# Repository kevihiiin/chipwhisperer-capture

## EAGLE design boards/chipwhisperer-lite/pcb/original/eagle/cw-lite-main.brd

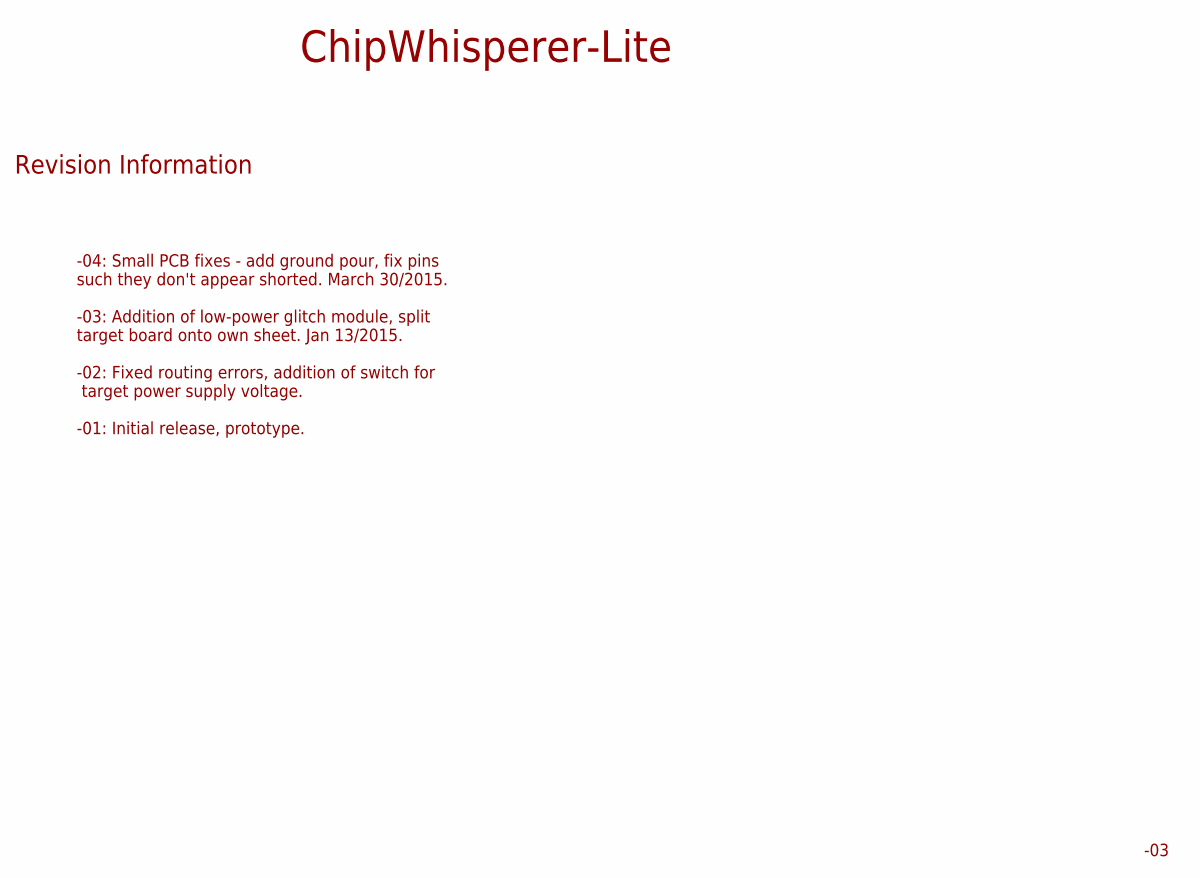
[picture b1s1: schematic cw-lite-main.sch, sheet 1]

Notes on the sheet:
-04: Small PCB fixes - add ground pour, fix pins such they don't appear shorted. March 30/2015. -03: Addition of low-power glitch module, split target board onto own sheet. Jan 13/2015. -02: Fixed routing errors, addition of switch for target power supply voltage. -01: Initial release, prototype.
ChipWhisperer-Lite
Revision Information

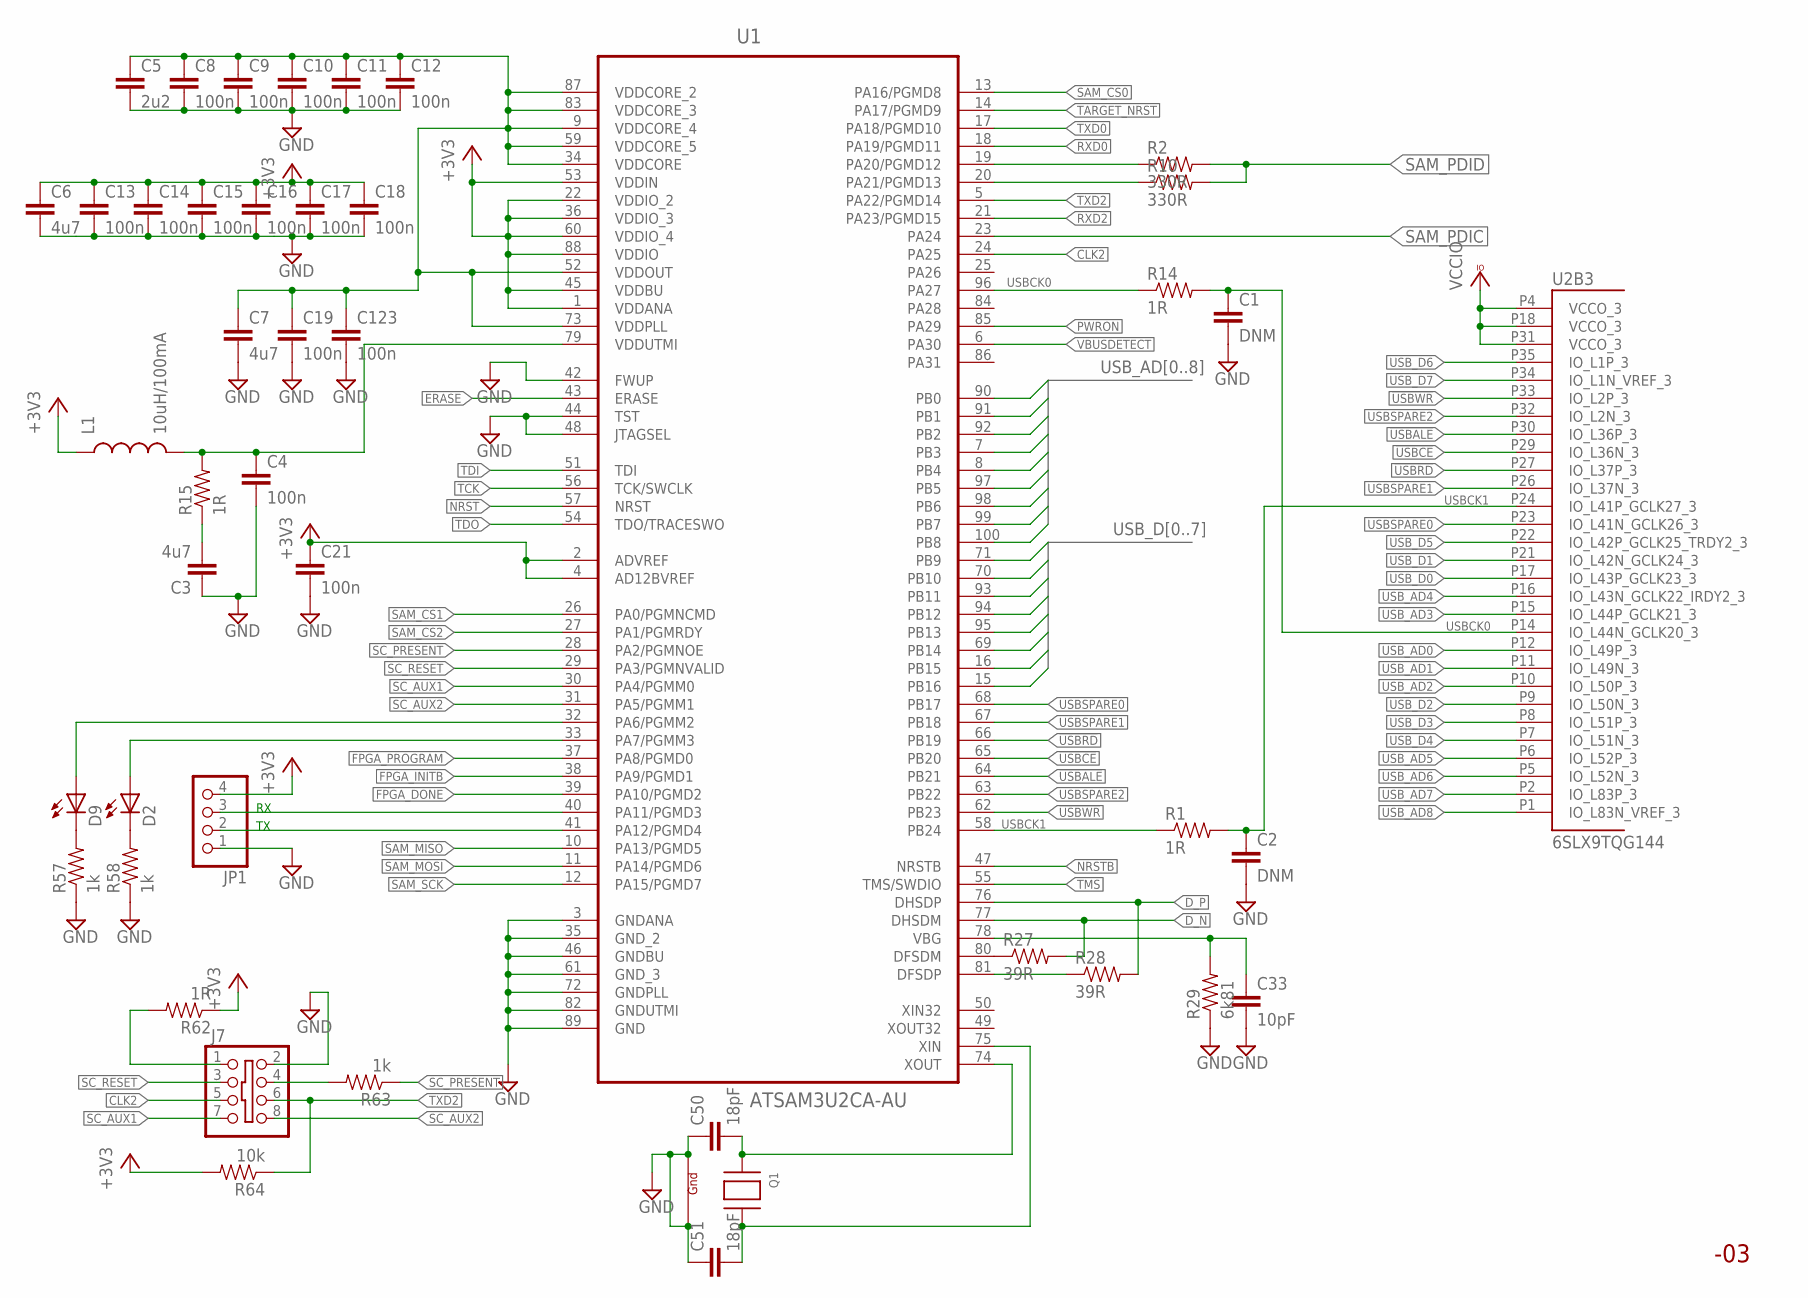
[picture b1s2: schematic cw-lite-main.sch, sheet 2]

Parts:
C1, C2: DNM; 0402C
C3, C6, C7: 4u7; 0603C
C4, C8, C9, C10, C11, C12, C13, C14, C15, C16, C17, C18, C19, C21, C123: 100n; 0402C
C5: 2u2; 0603C
C33: 10pF; 0603C
C50, C51: 18pF; 0402C
D2, D9: LED0603; LED-0603
J7: SHROUD_2X4EDGE; PINSHRD_EDGE_2X04.PAC
JP1: PINHD-1X4; 1X04
L1: 10uH/100mA; 0603
Q1: XTAL-4ABM8G; NX3225; MPN ABM8G-12.000MHZ-4Y-T3
R1, R14: 1R; 0402R
R2, R10: 330R; 0402R
R15, R62: 1R; 0603R
R27, R28: 39R; 0603R
R29: 6k81; 0402R
R57, R58, R63: 1k; 0603R
R64: 10k; 0603R
U1: ATSAM3U2CA-AU; QFP50P1600X1600X160-100N
U2: 6SLX9TQG144; TQ144; MPN XC6SLX9-3TQG144C

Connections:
!USBALE: U1.64 (PB21), U2.P30 (IO_L36P_3)
!USBCE: U1.65 (PB20), U2.P29 (IO_L36N_3)
!USBRD: U1.66 (PB19), U2.P27 (IO_L37P_3)
!USBWR: U1.62 (PB23), U2.P33 (IO_L2P_3)
+3V3: C6.1, C13.1, C14.1, C15.1, C16.1, C17.1, C18.1, C21.1, JP1.4, L1.1, R62.1, R64.2, U1.1 (VDDANA), U1.2 (ADVREF), U1.4 (AD12BVREF), U1.22 (VDDIO_2), U1.36 (VDDIO_3), U1.45 (VDDBU), U1.53 (VDDIN), U1.60 (VDDIO_4), U1.88 (VDDIO); also elsewhere on the board
CLK2: J7.5, U1.24 (PA25); also elsewhere on the board
D_N: R27.2, U1.77 (DHSDM); also elsewhere on the board
D_P: R28.2, U1.76 (DHSDP); also elsewhere on the board
ERASE: U1.43 (ERASE); also elsewhere on the board
FPGA_DONE: U1.39 (PA10/PGMD2); also elsewhere on the board
FPGA_INITB: U1.38 (PA9/PGMD1); also elsewhere on the board
FPGA_PROGRAM: U1.37 (PA8/PGMD0); also elsewhere on the board
GND: C1.2, C2.2, C3.1, C4.2, C5.2, C6.2, C7.2, C8.2, C9.2, C10.2, C11.2, C12.2, C13.2, C14.2, C15.2, C16.2, C17.2, C18.2, C19.2, C21.2, C33.2, C50.1, C51.1, C123.2, J7.2, JP1.1, Q1.2 (G1), Q1.4 (G2), R29.1, R57.1, R58.1, U1.3 (GNDANA), U1.35 (GND_2), U1.42 (FWUP), U1.44 (TST), U1.46 (GNDBU), U1.48 (JTAGSEL), U1.61 (GND_3), U1.72 (GNDPLL), U1.82 (GNDUTMI), U1.89 (GND); also elsewhere on the board
unnamed: R14.1, U1.96 (PA27)
unnamed: JP1.3, U1.40 (PA11/PGMD3)
unnamed: R1.1, U1.58 (PB24)
unnamed: JP1.2, U1.41 (PA12/PGMD4)
unnamed: R2.1, U1.19 (PA20/PGMD12)
unnamed: R10.1, U1.20 (PA21/PGMD13)
unnamed: C3.2, R15.1
unnamed: C4.1, L1.2, R15.2, U1.79 (VDDUTMI)
unnamed: R27.1, U1.80 (DFSDM)
unnamed: C5.1, C7.1, C8.1, C9.1, C10.1, C11.1, C12.1, C19.1, C123.1, U1.9 (VDDCORE_4), U1.34 (VDDCORE), U1.52 (VDDOUT), U1.59 (VDDCORE_5), U1.73 (VDDPLL), U1.83 (VDDCORE_3), U1.87 (VDDCORE_2)
unnamed: R28.1, U1.81 (DFSDP)
unnamed: C33.1, R29.2, U1.78 (VBG)
unnamed: C51.2, Q1.3 (X2), U1.75 (XIN)
unnamed: C50.2, Q1.1 (X1), U1.74 (XOUT)
unnamed: D9.A, U1.32 (PA6/PGMM2)
unnamed: D2.A, U1.33 (PA7/PGMM3)
unnamed: D9.C, R57.2
unnamed: D2.C, R58.2
unnamed: J7.1, R62.2
unnamed: J7.4, R63.2
NRST: U1.57 (NRST); also elsewhere on the board
NRSTB: U1.47 (NRSTB); also elsewhere on the board
PWRON: U1.85 (PA29); also elsewhere on the board
RXD0: U1.18 (PA19/PGMD11); also elsewhere on the board
RXD2: U1.21 (PA23/PGMD15); also elsewhere on the board
SAM_CS0: U1.13 (PA16/PGMD8); also elsewhere on the board
SAM_CS1: U1.26 (PA0/PGMNCMD); also elsewhere on the board
SAM_CS2: U1.27 (PA1/PGMRDY)
SAM_MISO: U1.10 (PA13/PGMD5); also elsewhere on the board
SAM_MOSI: U1.11 (PA14/PGMD6); also elsewhere on the board
SAM_PDIC: U1.23 (PA24); also elsewhere on the board
SAM_PDID: R2.2, R10.2; also elsewhere on the board
SAM_SCK: U1.12 (PA15/PGMD7); also elsewhere on the board
SC_AUX1: J7.7, U1.30 (PA4/PGMM0); also elsewhere on the board
SC_AUX2: J7.8, U1.31 (PA5/PGMM1); also elsewhere on the board
SC_PRESENT: R63.1, U1.28 (PA2/PGMNOE)
SC_RESET: J7.3, U1.29 (PA3/PGMNVALID); also elsewhere on the board
TARGET_NRST: U1.14 (PA17/PGMD9); also elsewhere on the board
TCK: U1.56 (TCK/SWCLK); also elsewhere on the board
TDI: U1.51 (TDI); also elsewhere on the board
TDO: U1.54 (TDO/TRACESWO); also elsewhere on the board
TMS: U1.55 (TMS/SWDIO); also elsewhere on the board
TXD0: U1.17 (PA18/PGMD10); also elsewhere on the board
TXD2: J7.6, R64.1, U1.5 (PA22/PGMD14); also elsewhere on the board
USBCK0: C1.1, R14.2, U2.P14 (IO_L44N_GCLK20_3)
USBCK1: C2.1, R1.2, U2.P24 (IO_L41P_GCLK27_3)
USBSPARE0: U1.68 (PB17), U2.P23 (IO_L41N_GCLK26_3)
USBSPARE1: U1.67 (PB18), U2.P26 (IO_L37N_3)
USBSPARE2: U1.63 (PB22), U2.P32 (IO_L2N_3)
USB_AD0: U1.90 (PB0), U2.P12 (IO_L49P_3)
USB_AD1: U1.91 (PB1), U2.P11 (IO_L49N_3)
USB_AD2: U1.92 (PB2), U2.P10 (IO_L50P_3)
USB_AD3: U1.7 (PB3), U2.P15 (IO_L44P_GCLK21_3)
USB_AD4: U1.8 (PB4), U2.P16 (IO_L43N_GCLK22_IRDY2_3)
USB_AD5: U1.97 (PB5), U2.P6 (IO_L52P_3)
USB_AD6: U1.98 (PB6), U2.P5 (IO_L52N_3)
USB_AD7: U1.99 (PB7), U2.P2 (IO_L83P_3)
USB_AD8: U1.100 (PB8), U2.P1 (IO_L83N_VREF_3)
USB_D0: U1.71 (PB9), U2.P17 (IO_L43P_GCLK23_3)
USB_D1: U1.70 (PB10), U2.P21 (IO_L42N_GCLK24_3)
USB_D2: U1.93 (PB11), U2.P9 (IO_L50N_3)
USB_D3: U1.94 (PB12), U2.P8 (IO_L51P_3)
USB_D4: U1.95 (PB13), U2.P7 (IO_L51N_3)
USB_D5: U1.69 (PB14), U2.P22 (IO_L42P_GCLK25_TRDY2_3)
USB_D6: U1.16 (PB15), U2.P35 (IO_L1P_3)
USB_D7: U1.15 (PB16), U2.P34 (IO_L1N_VREF_3)
VBUSDETECT: U1.6 (PA30); also elsewhere on the board
VCCIO: U2.P4 (VCCO_3), U2.P18 (VCCO_3), U2.P31 (VCCO_3); also elsewhere on the board

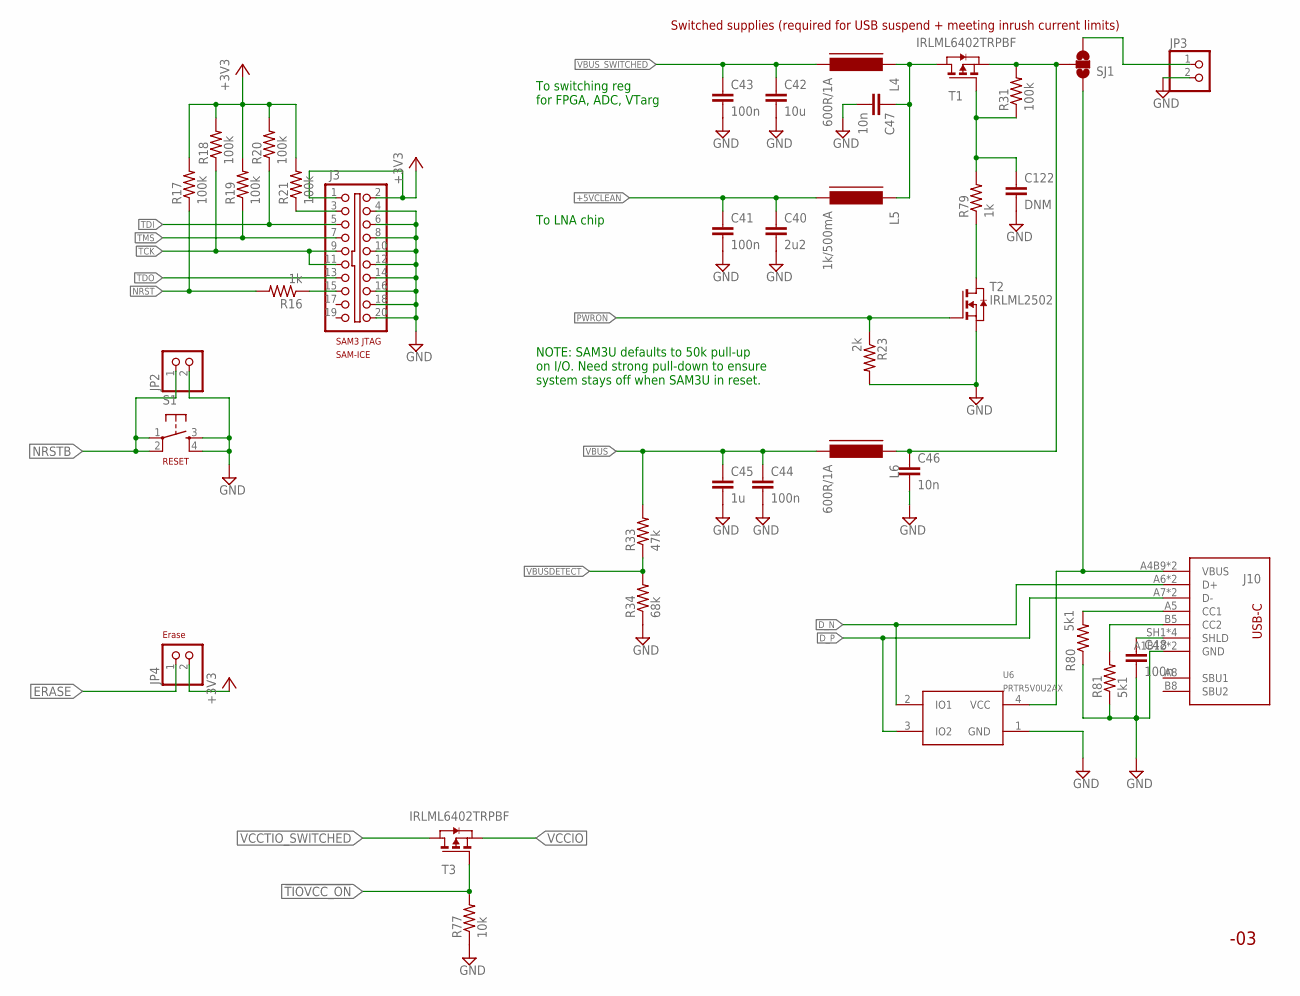
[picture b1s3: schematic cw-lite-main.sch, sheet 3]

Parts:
C40: 2u2; 0603C
C41, C43, C44, C48: 100n; 0603C
C42: 10u; 0603C
C45: 1u; 0603C
C46, C47: 10n; 0603C
C122: DNM; 0603C
J3: SHROUD_2X10-SHROUDED; PINSHRD_PTH_2X10
J10: USB Female Type C Connector; MOLEX_2171790001
JP2, JP3, JP4: PINHD-1X2; 1X02
L4, L6: 600R/1A; FB603
L5: 1k/500mA; FB603
R16: 1k; 0402R
R17, R18, R19, R20, R21, R31: 100k; 0402R
R23: 2k; 0603R
R33: 47k; 0402R
R34: 68k; 0402R
R77: 10k; 0402R
R79: 1k; 0603R
R80, R81: 5k1; 0402R
S1: TAC_SWITCHSMD; TACTILE_SWITCH_SMD
SJ1: SOLDERJUMPER_2WAYPASTE1&2; SJ_3_PASTE1&2
T1, T3: IRLML6402TRPBF; SOT-23; MPN IRLML6402TRPBF
T2: IRLML2502; SOT-23; MPN IRLML2502TRPBF
U6: PRTR5V0U2AX; SOT143B; MPN PRTR5V0U2AX,215

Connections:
!TIOVCC_ON: R77.2, T3.3 (G); also elsewhere on the board
+3V3: J3.1, J3.2, JP4.2, R17.2, R18.2, R19.2, R20.2, R21.2; also elsewhere on the board
+5VCLEAN: C40.1, C41.1, L5.2; also elsewhere on the board
D_N: J10.A6 (D+), J10.B6 (D+), U6.2 (IO1); also elsewhere on the board
D_P: J10.A7 (D-), J10.B7 (D-), U6.3 (IO2); also elsewhere on the board
ERASE: JP4.1; also elsewhere on the board
GND: C40.2, C41.2, C42.2, C43.2, C44.2, C45.2, C46.2, C47.2, C48.2, C122.2, J3.4, J3.6, J3.8, J3.10, J3.12, J3.14, J3.16, J3.18, J3.20, J10.A1B12 (GND), J10.B1A12 (GND), JP2.2, JP3.2, R23.2, R34.1, R77.1, R80.1, R81.1, S1.3, S1.4, T2.2 (S), U6.1 (GND); also elsewhere on the board
unnamed: J3.3, R21.1
unnamed: J3.15, R16.1
unnamed: C48.1, J10.SH1 (SHLD), J10.SH2 (SHLD), J10.SH3 (SHLD), J10.SH4 (SHLD)
unnamed: JP3.1, SJ1.3
unnamed: C46.1, L6.1, R31.2, SJ1.2, T1.2 (S)
unnamed: J10.A4B9 (VBUS), J10.B4A9 (VBUS), SJ1.1, U6.4 (VCC)
unnamed: C47.1, L4.1, L5.1, T1.1 (D)
unnamed: C122.1, R31.1, R79.2, T1.3 (G)
unnamed: R79.1, T2.1 (D)
unnamed: J10.B5 (CC2), R81.2
unnamed: J10.A5 (CC1), R80.2
NRST: R16.2, R17.1; also elsewhere on the board
NRSTB: JP2.1, S1.1, S1.2; also elsewhere on the board
PWRON: R23.1, T2.3 (G); also elsewhere on the board
TCK: J3.9, J3.11, R18.1; also elsewhere on the board
TDI: J3.5, R20.1; also elsewhere on the board
TDO: J3.13; also elsewhere on the board
TMS: J3.7, R19.1; also elsewhere on the board
VBUS: C44.1, C45.1, L6.2, R33.2; also elsewhere on the board
VBUSDETECT: R33.1, R34.2; also elsewhere on the board
VBUS_SWITCHED: C42.1, C43.1, L4.2; also elsewhere on the board
VCCIO: T3.2 (S); also elsewhere on the board
VCCTIO_SWITCHED: T3.1 (D); also elsewhere on the board

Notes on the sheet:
SAM3 JTAG
SAM-ICE
RESET
Erase
Switched supplies (required for USB suspend + meeting inrush current limits)
NOTE: SAM3U defaults to 50k pull-up on I/O. Need strong pull-down to ensure system stays off when SAM3U in reset.
To switching reg for FPGA, ADC, VTarg
To LNA chip

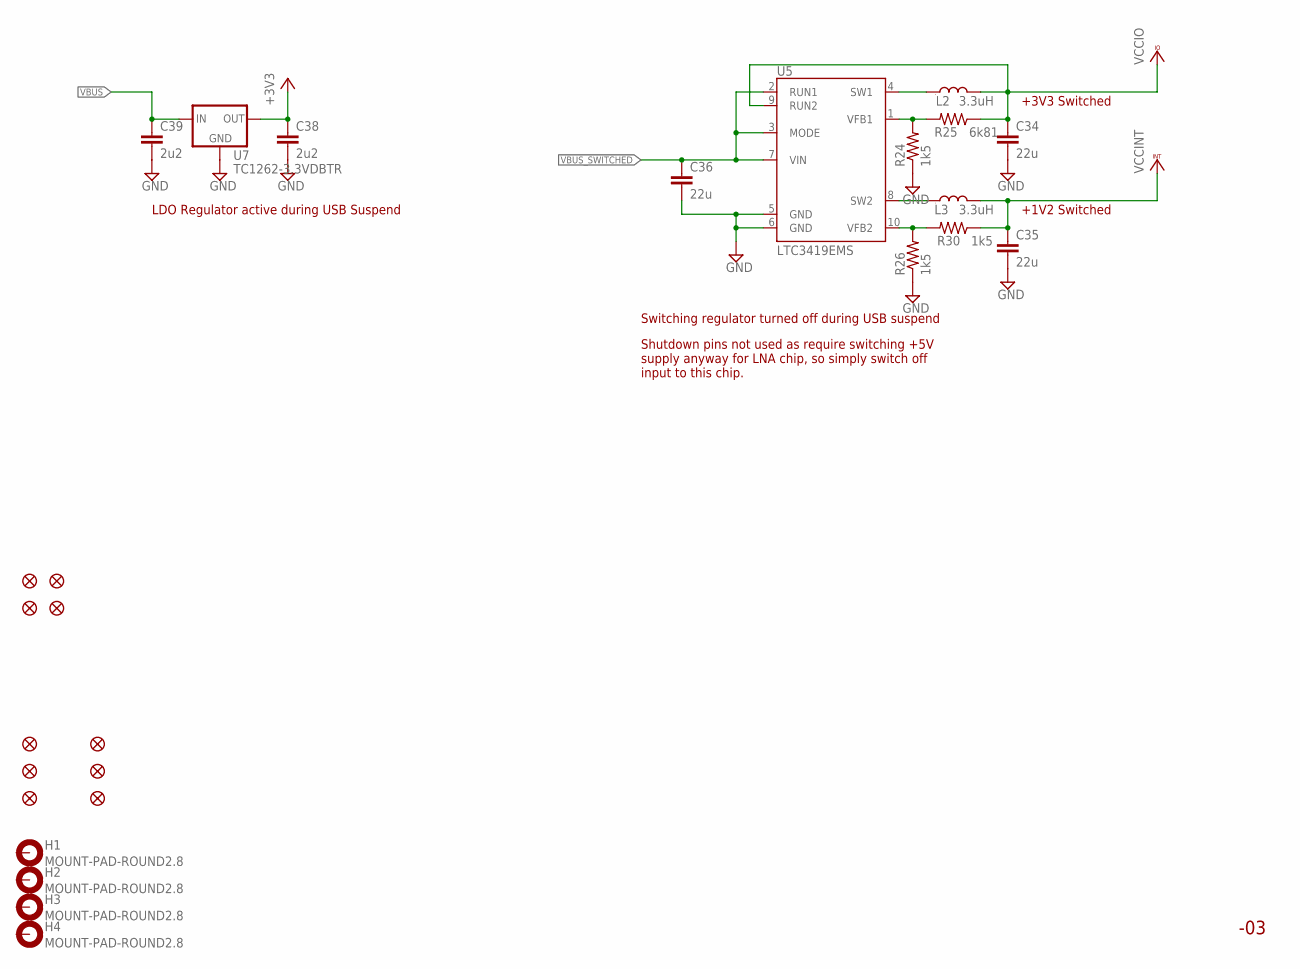
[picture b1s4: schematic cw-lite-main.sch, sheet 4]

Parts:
C34, C35, C36: 22u; 0805
C38, C39: 2u2; 0603C
FID1, FID2, FID3, FID4, FID5, FID6: FIDUCIAL1.5X3; FIDUCIAL-1.5X3
H1, H2, H3, H4: MOUNT-PAD-ROUND2.8; 2,8-PAD
L2: 3.3uH; VLS3015
L3: 3.3uH; VLS3015; MPN VLS3015ET-3R3M
MFID1, MFID2, MFID3, MFID4: FIDUCIALUFIDUCIAL; MICRO-FIDUCIAL
R24, R26, R30: 1k5; 0402R
R25: 6k81; 0402R
U5: LTC3419EMS; MSOP10; MPN LTC3419EMS#PBF
U7: TC1262-3.3VDBTR; SOT223; MPN TC1262-3.3VDBTR

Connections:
+3V3: C38.1, U7.3 (OUT); also elsewhere on the board
FB_1V2: R26.2, R30.2, U5.10 (VFB2)
FB_3V3: R24.2, R25.2, U5.1 (VFB1)
GND: C34.2, C35.2, C36.2, C38.2, C39.2, R24.1, R26.1, U5.5 (GND), U5.6 (GND), U7.2 (GND); also elsewhere on the board
unnamed: L2.1, U5.4 (SW1)
unnamed: L3.1, U5.8 (SW2)
VBUS: C39.1, U7.1 (IN); also elsewhere on the board
VBUS_SWITCHED: C36.1, U5.2 (RUN1), U5.3 (MODE), U5.7 (VIN); also elsewhere on the board
VCCINT: C35.1, L3.2, R30.1; also elsewhere on the board
VCCIO: C34.1, L2.2, R25.1, U5.9 (RUN2); also elsewhere on the board

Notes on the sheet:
+3V3 Switched
+1V2 Switched
LDO Regulator active during USB Suspend
Switching regulator turned off during USB suspend
Shutdown pins not used as require switching +5V supply anyway for LNA chip, so simply switch off input to this chip.

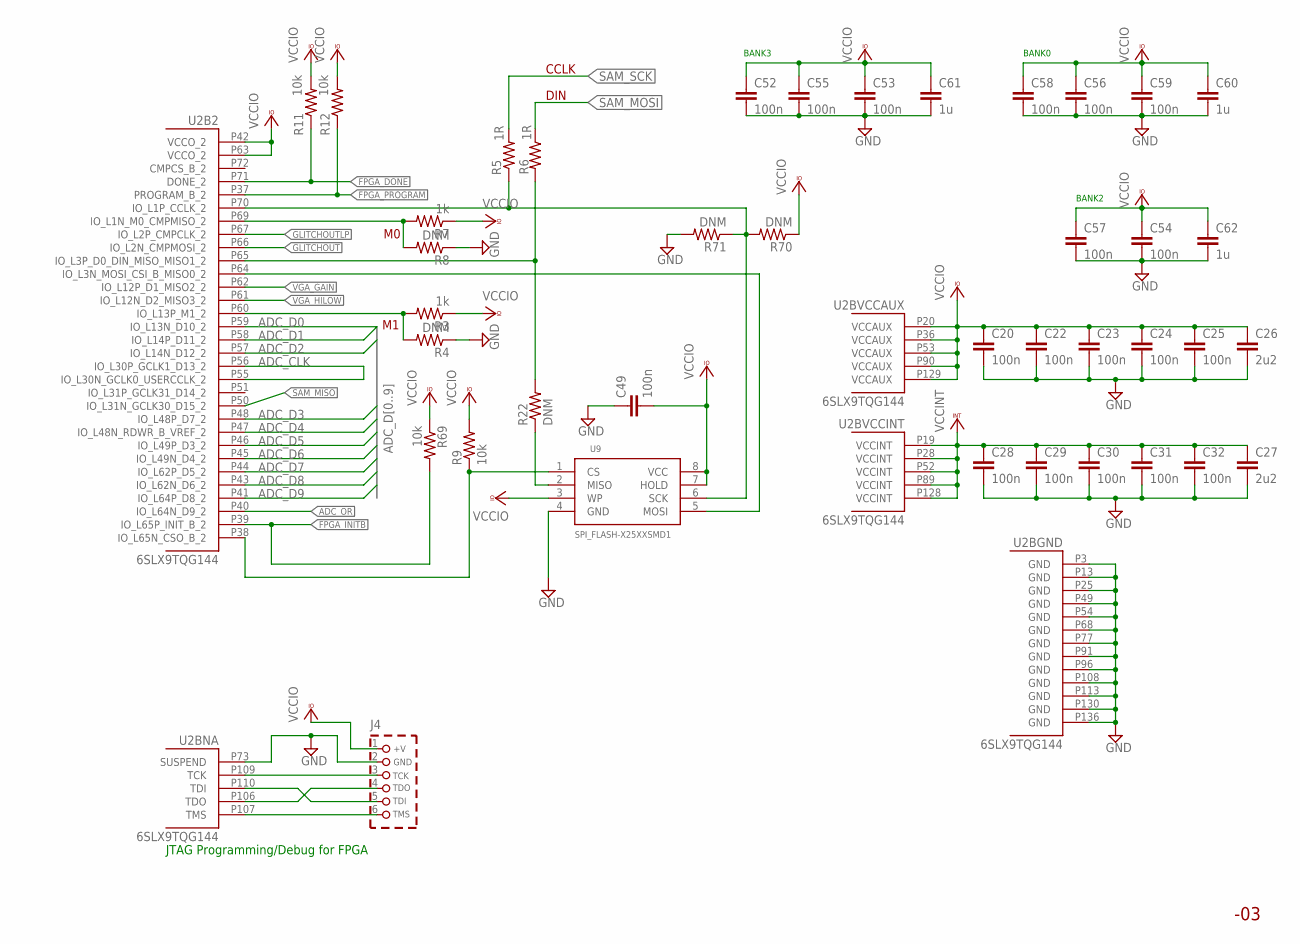
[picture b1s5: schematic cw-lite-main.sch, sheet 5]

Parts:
C20, C22, C23, C24, C25, C28, C29, C30, C31, C32, C52, C53, C54, C55, C56, C57, C58, C59: 100n; 0402C
C26, C27: 2u2; 0603C
C49: 100n; 0603C
C60, C61, C62: 1u; 0603C
J4: CON_HEADER_PRG_XILINX_JTAG6; HEADER_PRG_1X06
R3, R7: 1k; 0603R
R4, R8, R22: DNM; 0603R
R5, R6: 1R; 0402R
R9, R11, R12, R69: 10k; 0402R
R70, R71: DNM; 0402R
U2: 6SLX9TQG144; TQ144; MPN XC6SLX9-3TQG144C
U9: SPI_FLASH-X25XXSMD1; SO08-EIAJ

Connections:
ADC_CLK: U2.P55 (IO_L30N_GCLK0_USERCCLK_2), U2.P56 (IO_L30P_GCLK1_D13_2); also elsewhere on the board
ADC_D0: U2.P59 (IO_L13N_D10_2); also elsewhere on the board
ADC_D1: U2.P58 (IO_L14P_D11_2); also elsewhere on the board
ADC_D2: U2.P57 (IO_L14N_D12_2); also elsewhere on the board
ADC_D3: U2.P48 (IO_L48P_D7_2); also elsewhere on the board
ADC_D4: U2.P47 (IO_L48N_RDWR_B_VREF_2); also elsewhere on the board
ADC_D5: U2.P46 (IO_L49P_D3_2); also elsewhere on the board
ADC_D6: U2.P45 (IO_L49N_D4_2); also elsewhere on the board
ADC_D7: U2.P44 (IO_L62P_D5_2); also elsewhere on the board
ADC_D8: U2.P43 (IO_L62N_D6_2); also elsewhere on the board
ADC_D9: U2.P41 (IO_L64P_D8_2); also elsewhere on the board
ADC_OR: U2.P40 (IO_L64N_D9_2); also elsewhere on the board
FPGA_DONE: R11.1, U2.P71 (DONE_2); also elsewhere on the board
FPGA_INITB: R69.2, U2.P39 (IO_L65P_INIT_B_2); also elsewhere on the board
FPGA_PROGRAM: R12.1, U2.P37 (PROGRAM_B_2); also elsewhere on the board
GLITCHOUT: U2.P66 (IO_L2N_CMPMOSI_2); also elsewhere on the board
GLITCHOUTLP: U2.P67 (IO_L2P_CMPCLK_2); also elsewhere on the board
GND: C20.2, C22.2, C23.2, C24.2, C25.2, C26.2, C27.2, C28.2, C29.2, C30.2, C31.2, C32.2, C49.1, C52.2, C53.2, C54.2, C55.2, C56.2, C57.2, C58.2, C59.2, C60.2, C61.2, C62.2, J4.2 (GND), R4.1, R8.1, R71.2, U2.P3 (GND), U2.P13 (GND), U2.P25 (GND), U2.P49 (GND), U2.P54 (GND), U2.P68 (GND), U2.P73 (SUSPEND), U2.P77 (GND), U2.P91 (GND), U2.P96 (GND), U2.P108 (GND), U2.P113 (GND), U2.P130 (GND), U2.P136 (GND), U9.4 (GND); also elsewhere on the board
unnamed: R5.1, R70.2, R71.1, U2.P70 (IO_L1P_CCLK_2), U9.6 (SCK)
unnamed: R9.1, U2.P38 (IO_L65N_CSO_B_2), U9.1 (CS)
unnamed: R3.2, R4.2, U2.P60 (IO_L13P_M1_2)
unnamed: R7.2, R8.2, U2.P69 (IO_L1N_M0_CMPMISO_2)
unnamed: U2.P64 (IO_L3N_MOSI_CSI_B_MISO0_2), U9.5 (MOSI)
unnamed: R6.2, R22.2, U2.P65 (IO_L3P_D0_DIN_MISO_MISO1_2)
unnamed: R22.1, U9.2 (MISO)
unnamed: J4.6 (TMS), U2.P107 (TMS)
unnamed: J4.5 (TDI), U2.P110 (TDI)
unnamed: J4.4 (TDO), U2.P106 (TDO)
unnamed: J4.3 (TCK), U2.P109 (TCK)
SAM_MISO: U2.P50 (IO_L31N_GCLK30_D15_2); also elsewhere on the board
SAM_MOSI: R6.1; also elsewhere on the board
SAM_SCK: R5.2; also elsewhere on the board
VCCINT: C27.1, C28.1, C29.1, C30.1, C31.1, C32.1, U2.P19 (VCCINT), U2.P28 (VCCINT), U2.P52 (VCCINT), U2.P89 (VCCINT), U2.P128 (VCCINT); also elsewhere on the board
VCCIO: C20.1, C22.1, C23.1, C24.1, C25.1, C26.1, C49.2, C52.1, C53.1, C54.1, C55.1, C56.1, C57.1, C58.1, C59.1, C60.1, C61.1, C62.1, J4.1 (+V), R3.1, R7.1, R9.2, R11.2, R12.2, R69.1, R70.1, U2.P20 (VCCAUX), U2.P36 (VCCAUX), U2.P42 (VCCO_2), U2.P53 (VCCAUX), U2.P63 (VCCO_2), U2.P90 (VCCAUX), U2.P129 (VCCAUX), U9.3 (WP), U9.7 (HOLD), U9.8 (VCC); also elsewhere on the board
VGA_GAIN: U2.P62 (IO_L12P_D1_MISO2_2); also elsewhere on the board
VGA_HILOW: U2.P61 (IO_L12N_D2_MISO3_2); also elsewhere on the board

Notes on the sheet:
BANK2
BANK3
BANK0
CCLK
DIN
JTAG Programming/Debug for FPGA

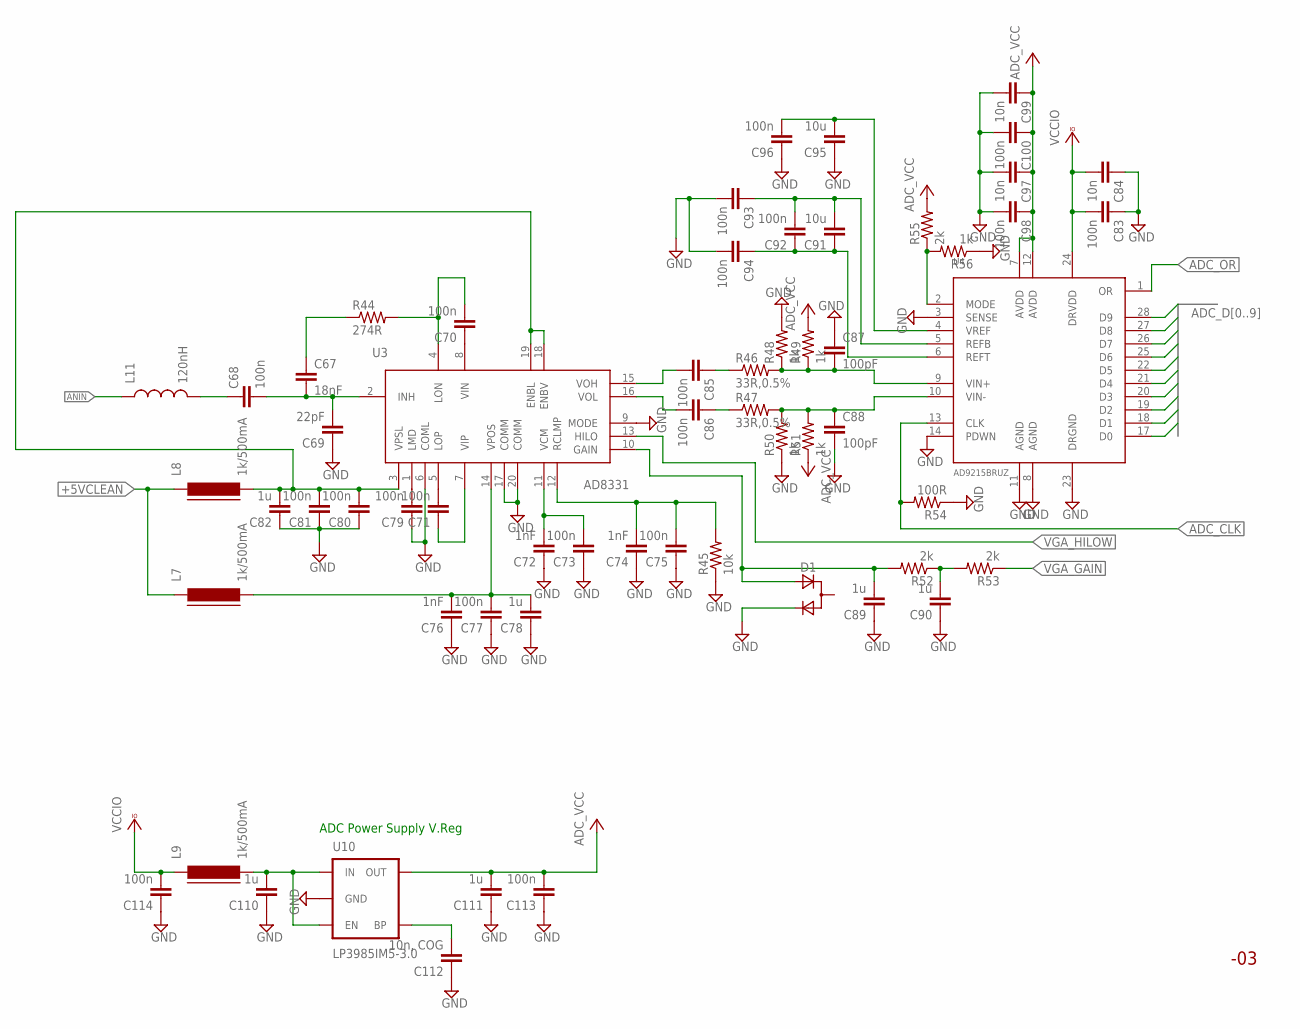
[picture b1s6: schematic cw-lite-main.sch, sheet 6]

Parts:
C67: 18nF; 0603C
C68, C85, C86: 100n; 0603C
C69: 22pF; 0603C
C70, C71, C73, C75, C77, C79, C80, C81, C83, C92, C93, C94, C96, C98, C100, C113, C114: 100n; 0402C
C72, C74, C76: 1nF; 0402C
C78, C82, C89, C90, C110, C111: 1u; 0603C
C84, C97, C99: 10n; 0402C
C87, C88: 100pF; 0603C
C91, C95: 10u; 0603C
C112: 10n, COG; 0402C
D1: D_ACACSOT23; SOT-23; MPN BAV99-7F
L7, L8, L9: 1k/500mA; FB603
L11: 120nH; 0603
R44: 274R; 0603R
R45: 10k; 0603R
R46, R47: 33R,0.5%; 0603R
R48, R49, R50, R51: 1k; 0402R
R52, R53, R55: 2k; 0603R
R54: 100R; 0603R
R56: 1k; 0603R
U3: AD8331; QSOP20; MPN AD8331ARQZ
U4: AD9215BRUZ; TSSOP28; MPN AD9215BRUZ-105
U10: LP3985IM5-3.0; SOT23-5; MPN LP3985IM5X-3.0/NOPB

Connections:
+5VCLEAN: L7.1, L8.1; also elsewhere on the board
ADC_CLK: R54.2, U4.13 (CLK); also elsewhere on the board
ADC_D0: U4.17 (D0); also elsewhere on the board
ADC_D1: U4.18 (D1); also elsewhere on the board
ADC_D2: U4.19 (D2); also elsewhere on the board
ADC_D3: U4.20 (D3); also elsewhere on the board
ADC_D4: U4.21 (D4); also elsewhere on the board
ADC_D5: U4.22 (D5); also elsewhere on the board
ADC_D6: U4.25 (D6); also elsewhere on the board
ADC_D7: U4.26 (D7); also elsewhere on the board
ADC_D8: U4.27 (D8); also elsewhere on the board
ADC_D9: U4.28 (D9); also elsewhere on the board
ADC_OR: U4.1 (OR); also elsewhere on the board
ADC_VCC: C97.1, C98.1, C99.1, C100.1, C111.2, C113.2, R49.2, R51.1, R55.2, U4.7 (AVDD), U4.12 (AVDD), U10.5 (OUT)
ANIN: L11.1; also elsewhere on the board
GND: C69.1, C72.1, C73.1, C74.1, C75.1, C76.1, C77.1, C78.1, C79.1, C80.1, C81.1, C82.1, C83.1, C84.1, C87.1, C88.2, C89.1, C90.1, C93.2, C94.2, C95.1, C96.1, C97.2, C98.2, C99.2, C100.2, C110.1, C111.1, C112.1, C113.1, C114.1, D1.2 (C), R45.1, R48.2, R50.1, R54.1, R56.1, U3.6 (COML), U3.9 (MODE), U3.17 (COMM), U3.20 (COMM), U4.3 (SENSE), U4.8 (AGND), U4.11 (AGND), U4.14 (PDWN), U4.23 (DRGND), U10.2 (GND); also elsewhere on the board
unnamed: C68.1, L11.2
unnamed: C110.2, L9.2, U10.1 (IN), U10.3 (EN)
unnamed: C112.2, U10.4 (BP)
unnamed: C67.2, C68.2, C69.2, U3.2 (INH)
unnamed: C70.2, R44.2, U3.4 (LON)
unnamed: C67.1, R44.1
unnamed: C70.1, U3.8 (VIN)
unnamed: C71.2, U3.5 (LOP)
unnamed: C74.2, C75.2, R45.2, U3.12 (RCLMP)
unnamed: C72.2, C73.2, U3.11 (VCM)
unnamed: C79.2, U3.1 (LMD)
unnamed: C89.2, D1.3 (A), R52.2, U3.10 (GAIN)
unnamed: C80.2, C81.2, C82.2, L8.2, U3.3 (VPSL), U3.18 (ENBV), U3.19 (ENBL)
unnamed: C71.1, U3.7 (VIP)
unnamed: C76.2, C77.2, C78.2, L7.2, U3.14 (VPOS)
unnamed: C87.2, R46.2, R48.1, R49.1, U4.9 (VIN+)
unnamed: C88.1, R47.2, R50.2, R51.2, U4.10 (VIN-)
unnamed: C85.2, U3.15 (VOH)
unnamed: C86.2, U3.16 (VOL)
unnamed: C85.1, R46.1
unnamed: C86.1, R47.1
unnamed: C91.2, C92.2, C93.1, U4.5 (REFB)
unnamed: C91.1, C92.1, C94.1, U4.6 (REFT)
unnamed: C90.2, R52.1, R53.2
unnamed: C95.2, C96.2, U4.4 (VREF)
unnamed: R55.1, R56.2, U4.2 (MODE)
VCCIO: C83.2, C84.2, C114.2, L9.1, U4.24 (DRVDD); also elsewhere on the board
VGA_GAIN: R53.1; also elsewhere on the board
VGA_HILOW: U3.13 (HILO); also elsewhere on the board

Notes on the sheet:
ADC Power Supply V.Reg

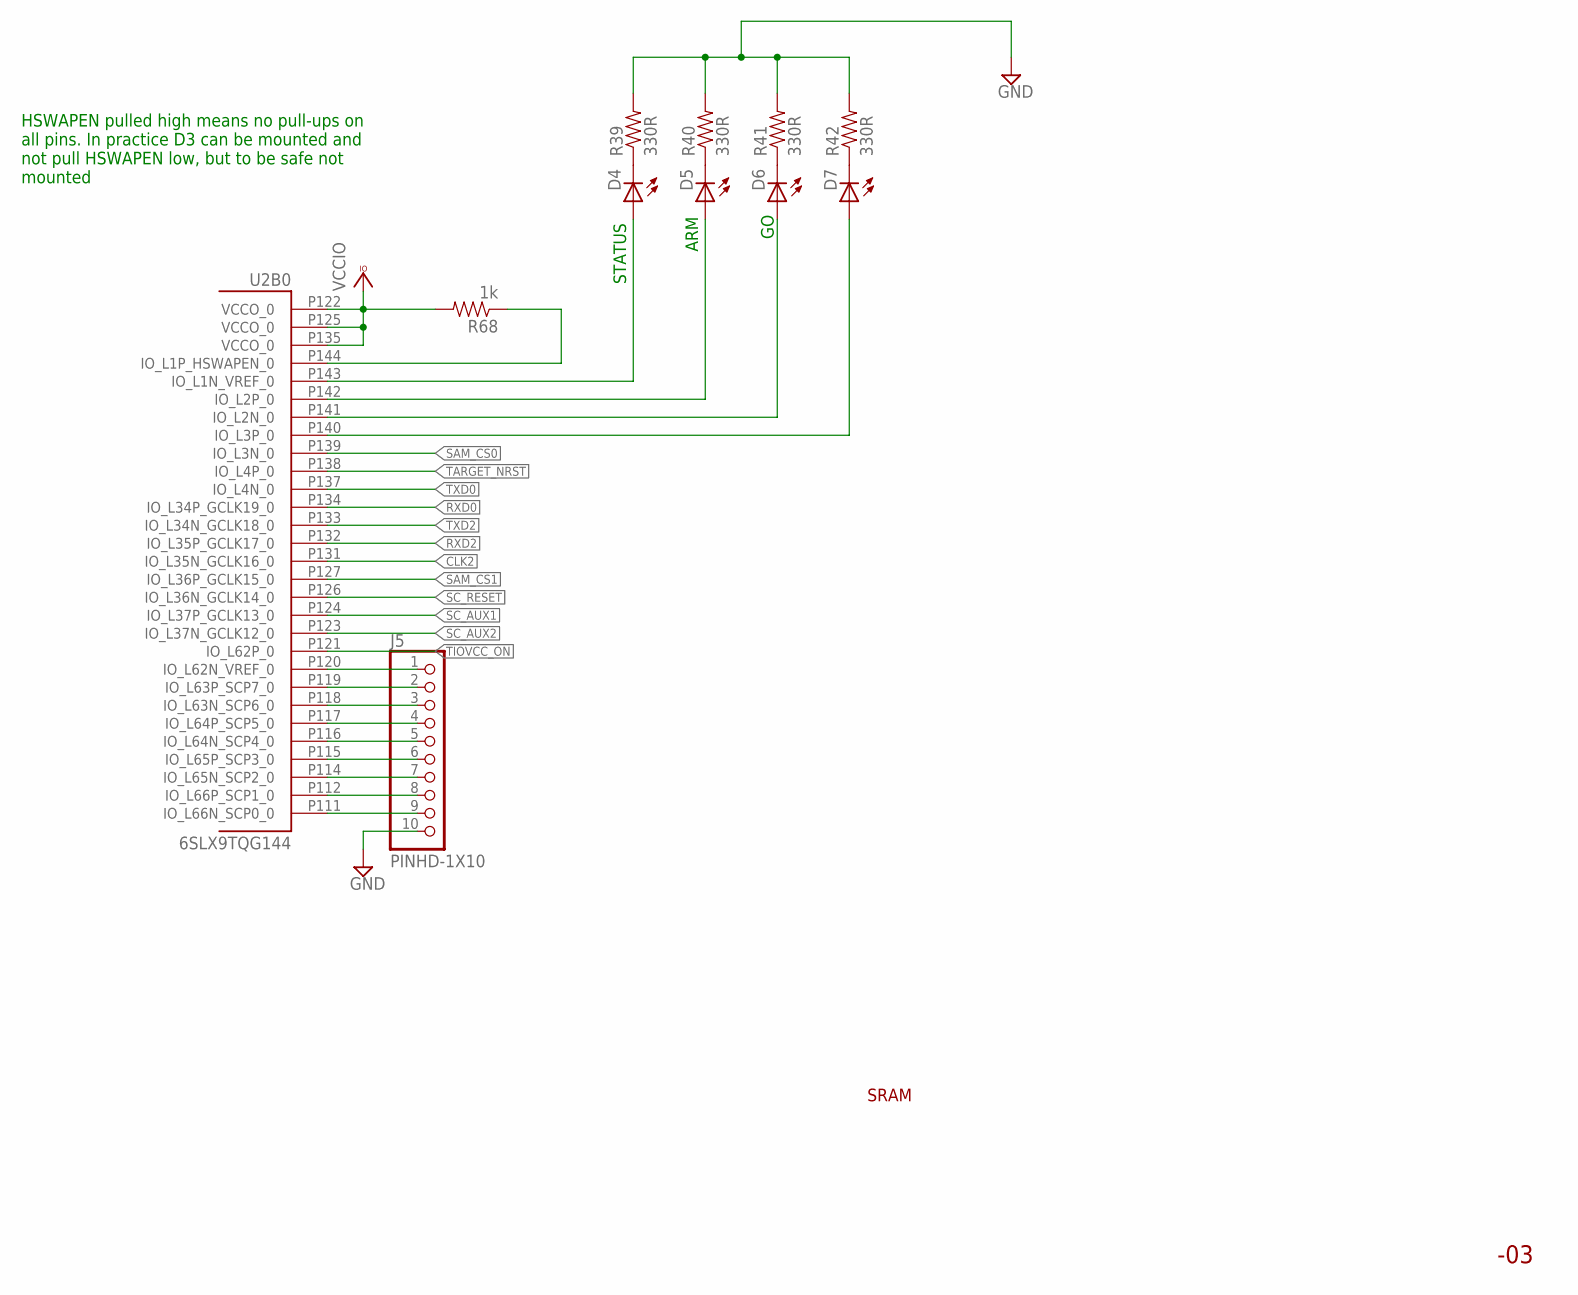
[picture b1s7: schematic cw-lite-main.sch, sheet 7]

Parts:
D4, D5, D6, D7: LED0603; LED-0603
J5: PINHD-1X10; 1X10-BIG
R39, R40, R41, R42: 330R; 0402R
R68: 1k; 0402R
U2: 6SLX9TQG144; TQ144; MPN XC6SLX9-3TQG144C

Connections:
!TIOVCC_ON: U2.P121 (IO_L62P_0); also elsewhere on the board
CLK2: U2.P131 (IO_L35N_GCLK16_0); also elsewhere on the board
GND: J5.10, R39.2, R40.2, R41.2, R42.2; also elsewhere on the board
LED_ARMED: D6.A, U2.P141 (IO_L2N_0)
LED_CAPTURE: D5.A, U2.P142 (IO_L2P_0)
LED_STATUS: R68.1, U2.P144 (IO_L1P_HSWAPEN_0)
LED_TCLOCK: D7.A, U2.P140 (IO_L3P_0)
LED_USBACT: D4.A, U2.P143 (IO_L1N_VREF_0)
unnamed: J5.1, U2.P120 (IO_L62N_VREF_0)
unnamed: J5.2, U2.P119 (IO_L63P_SCP7_0)
unnamed: J5.3, U2.P118 (IO_L63N_SCP6_0)
unnamed: J5.4, U2.P117 (IO_L64P_SCP5_0)
unnamed: J5.5, U2.P116 (IO_L64N_SCP4_0)
unnamed: J5.6, U2.P115 (IO_L65P_SCP3_0)
unnamed: J5.7, U2.P114 (IO_L65N_SCP2_0)
unnamed: J5.8, U2.P112 (IO_L66P_SCP1_0)
unnamed: J5.9, U2.P111 (IO_L66N_SCP0_0)
unnamed: D4.C, R39.1
unnamed: D5.C, R40.1
unnamed: D6.C, R41.1
unnamed: D7.C, R42.1
RXD0: U2.P134 (IO_L34P_GCLK19_0); also elsewhere on the board
RXD2: U2.P132 (IO_L35P_GCLK17_0); also elsewhere on the board
SAM_CS0: U2.P139 (IO_L3N_0); also elsewhere on the board
SAM_CS1: U2.P127 (IO_L36P_GCLK15_0); also elsewhere on the board
SC_AUX1: U2.P124 (IO_L37P_GCLK13_0); also elsewhere on the board
SC_AUX2: U2.P123 (IO_L37N_GCLK12_0); also elsewhere on the board
SC_RESET: U2.P126 (IO_L36N_GCLK14_0); also elsewhere on the board
TARGET_NRST: U2.P138 (IO_L4P_0); also elsewhere on the board
TXD0: U2.P137 (IO_L4N_0); also elsewhere on the board
TXD2: U2.P133 (IO_L34N_GCLK18_0); also elsewhere on the board
VCCIO: R68.2, U2.P122 (VCCO_0), U2.P125 (VCCO_0), U2.P135 (VCCO_0); also elsewhere on the board

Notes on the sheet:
SRAM
HSWAPEN pulled high means no pull-ups on all pins. In practice D3 can be mounted and not pull HSWAPEN low, but to be safe not mounted
STATUS
ARM

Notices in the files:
boards/chipwhisperer-lite/pcb/original/eagle/cw-lite-main.brd:
Copyright NewAE Technology Inc.
parts and their libraries:
SparkFun: Licensing: CC v3.0 Share-Alike You are welcome to use this library for commercial purposes.
SparkFun-PowerIC: Licensing: Creative Commons ShareAlike 4.0 International - https://creativecommons.org/licenses/by-sa/4.0
